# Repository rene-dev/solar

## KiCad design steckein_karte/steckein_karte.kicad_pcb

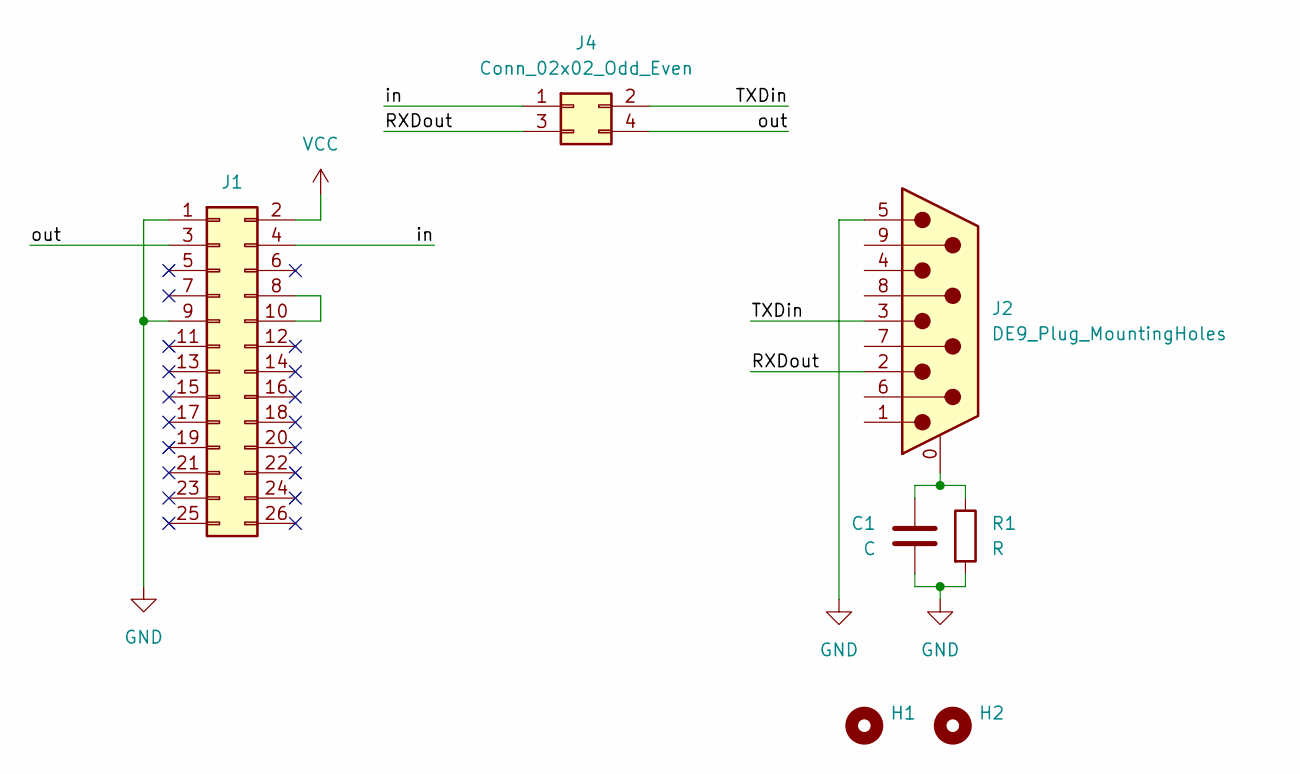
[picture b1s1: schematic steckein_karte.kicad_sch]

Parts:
C1: C; C_1812_4532Metric
H1, H2: MountingHole; MountingHole_2.7mm_M2.5
J1: Conn_02x13_Odd_Even; 02x13
J2: DE9_Plug_MountingHoles; DSUB-9_Female_Horizontal_P2.77x2.84mm_EdgePinOffset4.94mm_H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
J4: Conn_02x02_Odd_Even; PinHeader_2x02_P2.54mm_Vertical
R1: R; R_1812_4532Metric

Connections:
/RXDout: J2.2, J4.3
/TXDin: J2.3, J4.2
/in: J1.4, J4.1
/out: J1.3, J4.4
GND: C1.2, J1.1, J1.9, J2.5, R1.2
unnamed: J1.8, J1.10
unnamed: C1.1, J2.0 (PAD), R1.1
VCC: J1.2

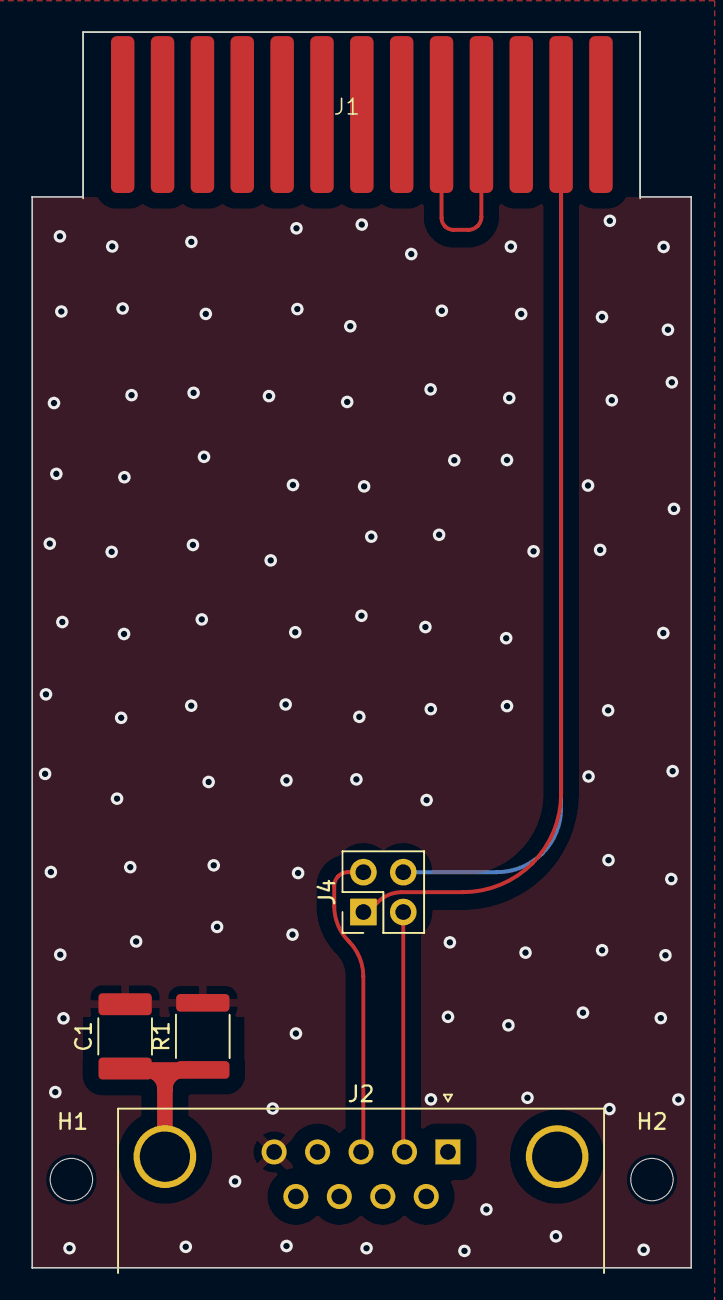
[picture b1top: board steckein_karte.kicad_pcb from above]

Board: 2 copper layers, 42.0 x 78.8 mm, 7 parts (0 on the bottom side), 7 nets.

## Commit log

2024-01-14 a d a p t e r
2024-01-14 G E R B E R
2024-01-15 pylon can
2024-02-02 round values
2024-02-02 add mqtt script
2024-02-02 add logging script
2024-02-18 systemd service
2024-04-11 hidraw
2025-03-16 mpi caml
2025-03-16 add mpi2
2025-03-24 update mpi config
